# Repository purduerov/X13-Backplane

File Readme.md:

# Readme for X13-Backplane

Whenever you make a new part, download the datasheet and save it here _**and**_ with the part in the parts library

Always pull other people's changes before beginning to work
`git pull`

Be sure to push your changes after  working on them. Run:
1. `git add .` to add any files in this directory or a subdirectory
or `git add -u` to add any modified files
2. (Optional) `git clean -nX` to see what ignored files can be removed
	`git clean -fX` removes ignored files (Eagle backups)
3. `git commit -m "helpful commit message"` with a description of the work that you did
4. `git push` to push your work to github

Other helpful commands
* `git status` says information about modified and staged files
* `git log` shows the recent commits of the repository
* `git log filename.extension` show the recent commits for just that file
* `git checkout first-couple-letter-of-commit-id` lets you go back to a previous version
* `git checkout master` brings you back to the latest commit
* `git tag` lists the tags
* `git tag -a orderX -m "the version of the board placed for the X'th order"` tag a specific commit
* `git push --tags` needed to push tags to remote
* `git show orderX` show the commit log for the given tag
* `git checkout orderX` go back and interact with the files at the tagged commit

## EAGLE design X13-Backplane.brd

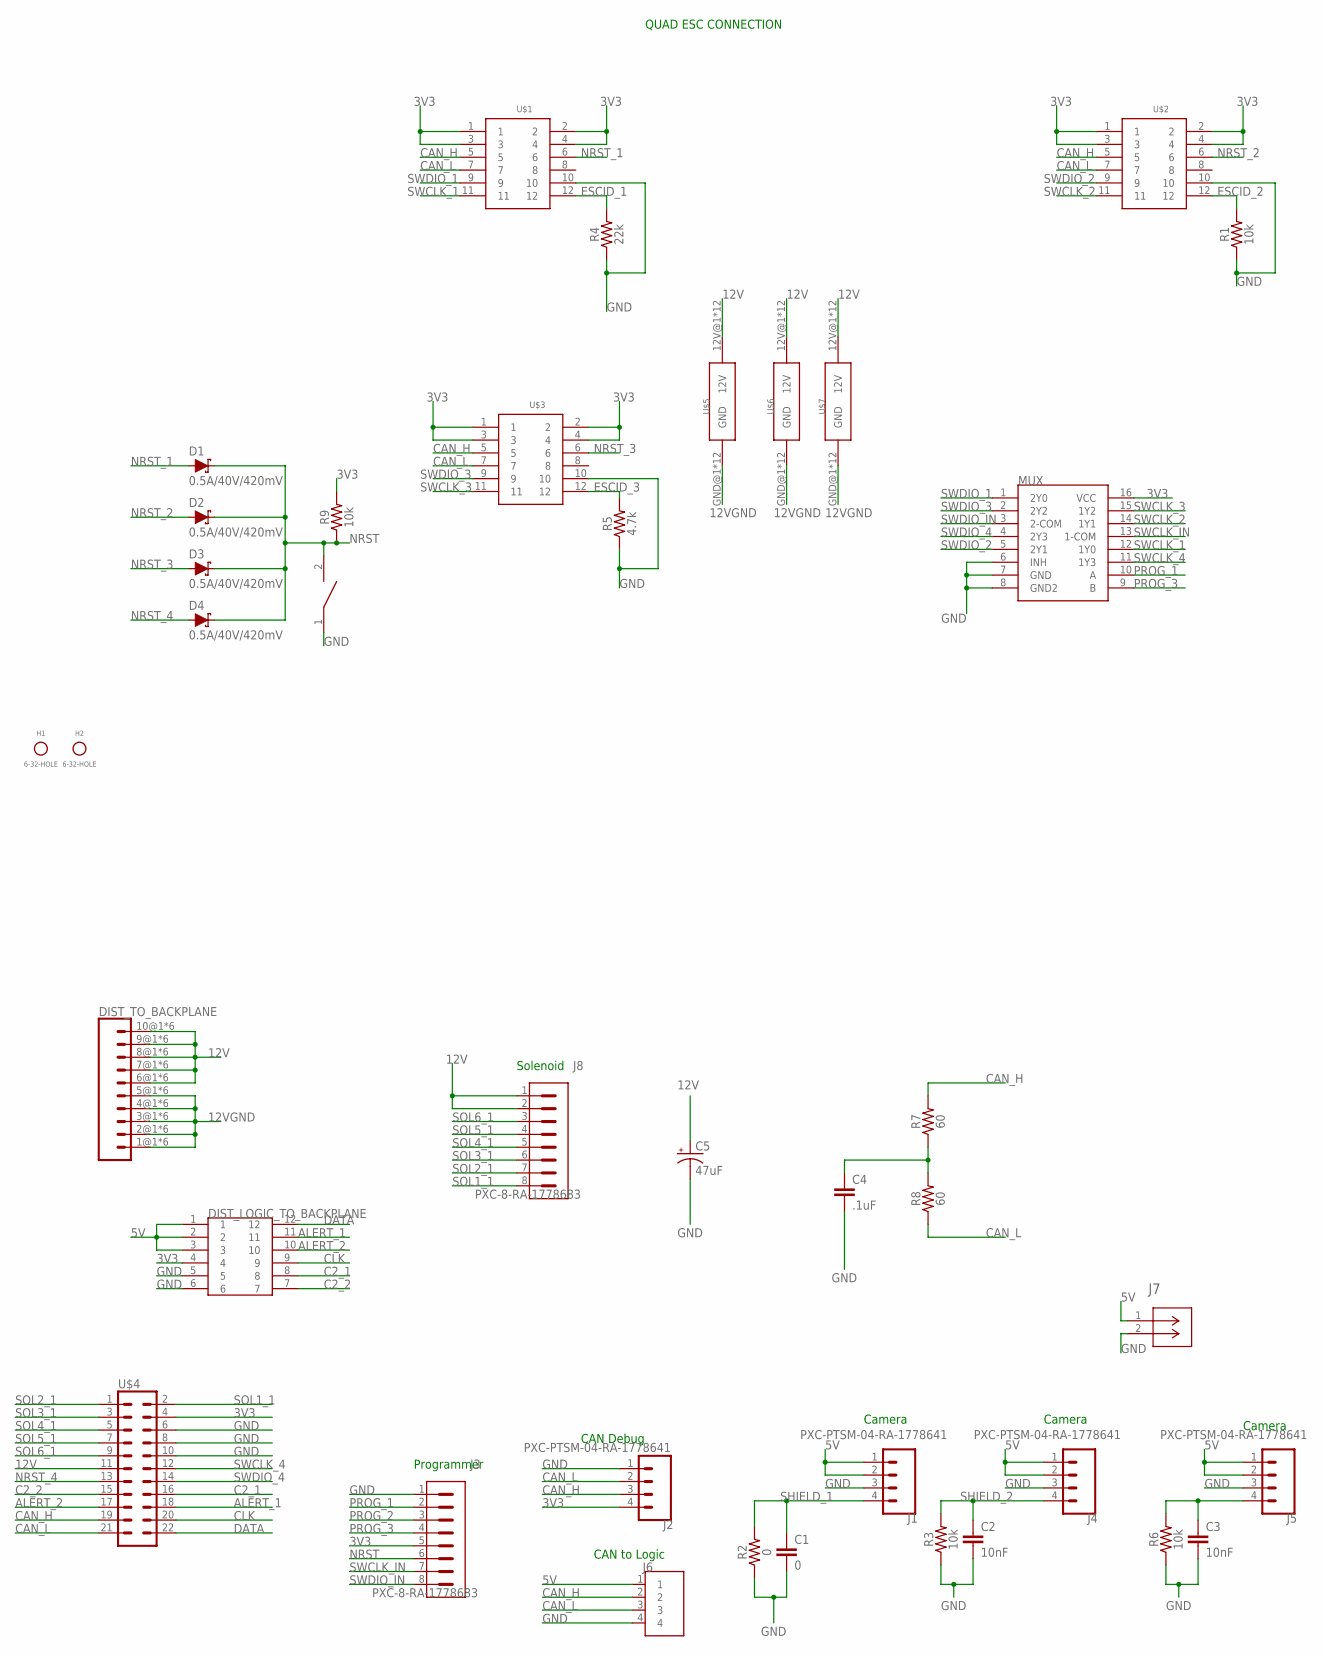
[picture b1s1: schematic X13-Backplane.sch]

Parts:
C1: 0; 0603
C2, C3: 10nF; 0603
C4: .1uF; 0603
C5: 47uF; PANASONIC_D
D1, D2, D3, D4: 0.5A/40V/420mV; SOD-323
DIST_LOGIC_TO_BACKPLANE: IPL1-106-01-L-D-K
DIST_TO_BACKPLANE: MPPT-10-01-01-L-RA-SD
H1, H2: 6-32-HOLE
J1, J2, J4, J5: PXC-PTSM-04-RA-1778641
J3, J8: PXC-8-RA-1778683
J6: 284512-4; TE_284512-4
J7: POE_TERMINAL; CONN2_282834-2_TEC
MUX: TI-SN74LV4052A; SOIC-16
R1, R3, R6, R9: 10k; 0603
R2: 0; 0603
R4: 22k; 0603
R5: 4.7k; 0603
R7, R8: 60; 0603
U$1, U$2, U$3: BACKPLANE_CONNECTORSBKP; BACKPLANE_CONNECTORS_BKP
U$4: BKP-TO-SOL; BKP-TO-SOL_TMM-111-01-T-D
U$5, U$6, U$7: BACKPLANE_ESC_ADAPTER_PWRBKP; BACKPLANE_ESC_ADAPTER_BKP_PWR
U$8: DISCRETECOMPONENTS_SWITCH; DISCRETECOMPONENTS_SW_2512

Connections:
3V3: DIST_LOGIC_TO_BACKPLANE.4, J2.4, J3.5, MUX.16 (VCC), R9.2, U$1.1, U$1.2, U$1.3, U$1.4, U$2.1, U$2.2, U$2.3, U$2.4, U$3.1, U$3.2, U$3.3, U$3.4, U$4.4
5V: DIST_LOGIC_TO_BACKPLANE.1, DIST_LOGIC_TO_BACKPLANE.2, DIST_LOGIC_TO_BACKPLANE.3, J1.1, J1.2, J4.1, J4.2, J5.1, J5.2, J6.1, J7.1
12V: C5.+, DIST_TO_BACKPLANE.6@1 (6), DIST_TO_BACKPLANE.6@2 (6), DIST_TO_BACKPLANE.6@3 (6), DIST_TO_BACKPLANE.6@4 (6), DIST_TO_BACKPLANE.6@5 (6), DIST_TO_BACKPLANE.6@6 (6), DIST_TO_BACKPLANE.7@1 (7), DIST_TO_BACKPLANE.7@2 (7), DIST_TO_BACKPLANE.7@3 (7), DIST_TO_BACKPLANE.7@4 (7), DIST_TO_BACKPLANE.7@5 (7), DIST_TO_BACKPLANE.7@6 (7), DIST_TO_BACKPLANE.8@1 (8), DIST_TO_BACKPLANE.8@2 (8), DIST_TO_BACKPLANE.8@3 (8), DIST_TO_BACKPLANE.8@4 (8), DIST_TO_BACKPLANE.8@5 (8), DIST_TO_BACKPLANE.8@6 (8), DIST_TO_BACKPLANE.9@1 (9), DIST_TO_BACKPLANE.9@2 (9), DIST_TO_BACKPLANE.9@3 (9), DIST_TO_BACKPLANE.9@4 (9), DIST_TO_BACKPLANE.9@5 (9), DIST_TO_BACKPLANE.9@6 (9), DIST_TO_BACKPLANE.10@1 (10), DIST_TO_BACKPLANE.10@2 (10), DIST_TO_BACKPLANE.10@3 (10), DIST_TO_BACKPLANE.10@4 (10), DIST_TO_BACKPLANE.10@5 (10), DIST_TO_BACKPLANE.10@6 (10), J8.1, J8.2, U$4.11, U$5.12V@1 (12V), U$5.12V@2 (12V), U$5.12V@3 (12V), U$5.12V@4 (12V), U$5.12V@5 (12V), U$5.12V@6 (12V), U$5.12V@7 (12V), U$5.12V@8 (12V), U$5.12V@9 (12V), U$5.12V@10 (12V), U$5.12V@11 (12V), U$5.12V@12 (12V), U$6.12V@1 (12V), U$6.12V@2 (12V), U$6.12V@3 (12V), U$6.12V@4 (12V), U$6.12V@5 (12V), U$6.12V@6 (12V), U$6.12V@7 (12V), U$6.12V@8 (12V), U$6.12V@9 (12V), U$6.12V@10 (12V), U$6.12V@11 (12V), U$6.12V@12 (12V), U$7.12V@1 (12V), U$7.12V@2 (12V), U$7.12V@3 (12V), U$7.12V@4 (12V), U$7.12V@5 (12V), U$7.12V@6 (12V), U$7.12V@7 (12V), U$7.12V@8 (12V), U$7.12V@9 (12V), U$7.12V@10 (12V), U$7.12V@11 (12V), U$7.12V@12 (12V)
12VGND: DIST_TO_BACKPLANE.1@1 (1), DIST_TO_BACKPLANE.1@2 (1), DIST_TO_BACKPLANE.1@3 (1), DIST_TO_BACKPLANE.1@4 (1), DIST_TO_BACKPLANE.1@5 (1), DIST_TO_BACKPLANE.1@6 (1), DIST_TO_BACKPLANE.2@1 (2), DIST_TO_BACKPLANE.2@2 (2), DIST_TO_BACKPLANE.2@3 (2), DIST_TO_BACKPLANE.2@4 (2), DIST_TO_BACKPLANE.2@5 (2), DIST_TO_BACKPLANE.2@6 (2), DIST_TO_BACKPLANE.3@1 (3), DIST_TO_BACKPLANE.3@2 (3), DIST_TO_BACKPLANE.3@3 (3), DIST_TO_BACKPLANE.3@4 (3), DIST_TO_BACKPLANE.3@5 (3), DIST_TO_BACKPLANE.3@6 (3), DIST_TO_BACKPLANE.4@1 (4), DIST_TO_BACKPLANE.4@2 (4), DIST_TO_BACKPLANE.4@3 (4), DIST_TO_BACKPLANE.4@4 (4), DIST_TO_BACKPLANE.4@5 (4), DIST_TO_BACKPLANE.4@6 (4), DIST_TO_BACKPLANE.5@1 (5), DIST_TO_BACKPLANE.5@2 (5), DIST_TO_BACKPLANE.5@3 (5), DIST_TO_BACKPLANE.5@4 (5), DIST_TO_BACKPLANE.5@5 (5), DIST_TO_BACKPLANE.5@6 (5), U$5.GND@1 (GND), U$5.GND@2 (GND), U$5.GND@3 (GND), U$5.GND@4 (GND), U$5.GND@5 (GND), U$5.GND@6 (GND), U$5.GND@7 (GND), U$5.GND@8 (GND), U$5.GND@9 (GND), U$5.GND@10 (GND), U$5.GND@11 (GND), U$5.GND@12 (GND), U$6.GND@1 (GND), U$6.GND@2 (GND), U$6.GND@3 (GND), U$6.GND@4 (GND), U$6.GND@5 (GND), U$6.GND@6 (GND), U$6.GND@7 (GND), U$6.GND@8 (GND), U$6.GND@9 (GND), U$6.GND@10 (GND), U$6.GND@11 (GND), U$6.GND@12 (GND), U$7.GND@1 (GND), U$7.GND@2 (GND), U$7.GND@3 (GND), U$7.GND@4 (GND), U$7.GND@5 (GND), U$7.GND@6 (GND), U$7.GND@7 (GND), U$7.GND@8 (GND), U$7.GND@9 (GND), U$7.GND@10 (GND), U$7.GND@11 (GND), U$7.GND@12 (GND)
ALERT_1: DIST_LOGIC_TO_BACKPLANE.11, U$4.18
ALERT_2: DIST_LOGIC_TO_BACKPLANE.10, U$4.17
C2_1: DIST_LOGIC_TO_BACKPLANE.8, U$4.16
C2_2: DIST_LOGIC_TO_BACKPLANE.7, U$4.15
CAN_H: J2.3, J6.2, R7.2, U$1.5, U$2.5, U$3.5, U$4.19
CAN_L: J2.2, J6.3, R8.1, U$1.7, U$2.7, U$3.7, U$4.21
CLK: DIST_LOGIC_TO_BACKPLANE.9, U$4.20
DATA: DIST_LOGIC_TO_BACKPLANE.12, U$4.22
ESCID_1: R4.2, U$1.12
ESCID_2: R1.2, U$2.12
ESCID_3: R5.2, U$3.12
GND: C1.2, C2.2, C3.2, C4.2, C5.-, DIST_LOGIC_TO_BACKPLANE.5, DIST_LOGIC_TO_BACKPLANE.6, J1.3, J2.1, J3.1, J4.3, J5.3, J6.4, J7.2, MUX.6 (INH), MUX.7 (GND), MUX.8 (GND2), R1.1, R2.1, R3.1, R4.1, R5.1, R6.1, U$1.10, U$2.10, U$3.10, U$4.6, U$4.8, U$4.10, U$8.1
unnamed: C4.1, R7.1, R8.2
NRST: D1.C, D2.C, D3.C, D4.C, J3.6, R9.1, U$8.2
NRST_1: D1.A, U$1.6
NRST_2: D2.A, U$2.6
NRST_3: D3.A, U$3.6
NRST_4: D4.A, U$4.13
PROG_1: J3.2, MUX.10 (A)
PROG_2: J3.3
PROG_3: J3.4, MUX.9 (B)
SHIELD_1: C1.1, J1.4, R2.2
SHIELD_2: C2.1, J4.4, R3.2
SHIELD_3: C3.1, J5.4, R6.2
SOL1_1: J8.8, U$4.2
SOL2_1: J8.7, U$4.1
SOL3_1: J8.6, U$4.3
SOL4_1: J8.5, U$4.5
SOL5_1: J8.4, U$4.7
SOL6_1: J8.3, U$4.9
SWCLK_1: MUX.12 (1Y0), U$1.11
SWCLK_2: MUX.14 (1Y1), U$2.11
SWCLK_3: MUX.15 (1Y2), U$3.11
SWCLK_4: MUX.11 (1Y3), U$4.12
SWCLK_IN: J3.7, MUX.13 (1-COM)
SWDIO_1: MUX.1 (2Y0), U$1.9
SWDIO_2: MUX.5 (2Y1), U$2.9
SWDIO_3: MUX.2 (2Y2), U$3.9
SWDIO_4: MUX.4 (2Y3), U$4.14
SWDIO_IN: J3.8, MUX.3 (2-COM)

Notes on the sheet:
CAN to Logic
CAN Debug
Programmer
QUAD ESC CONNECTION
Camera
Solenoid

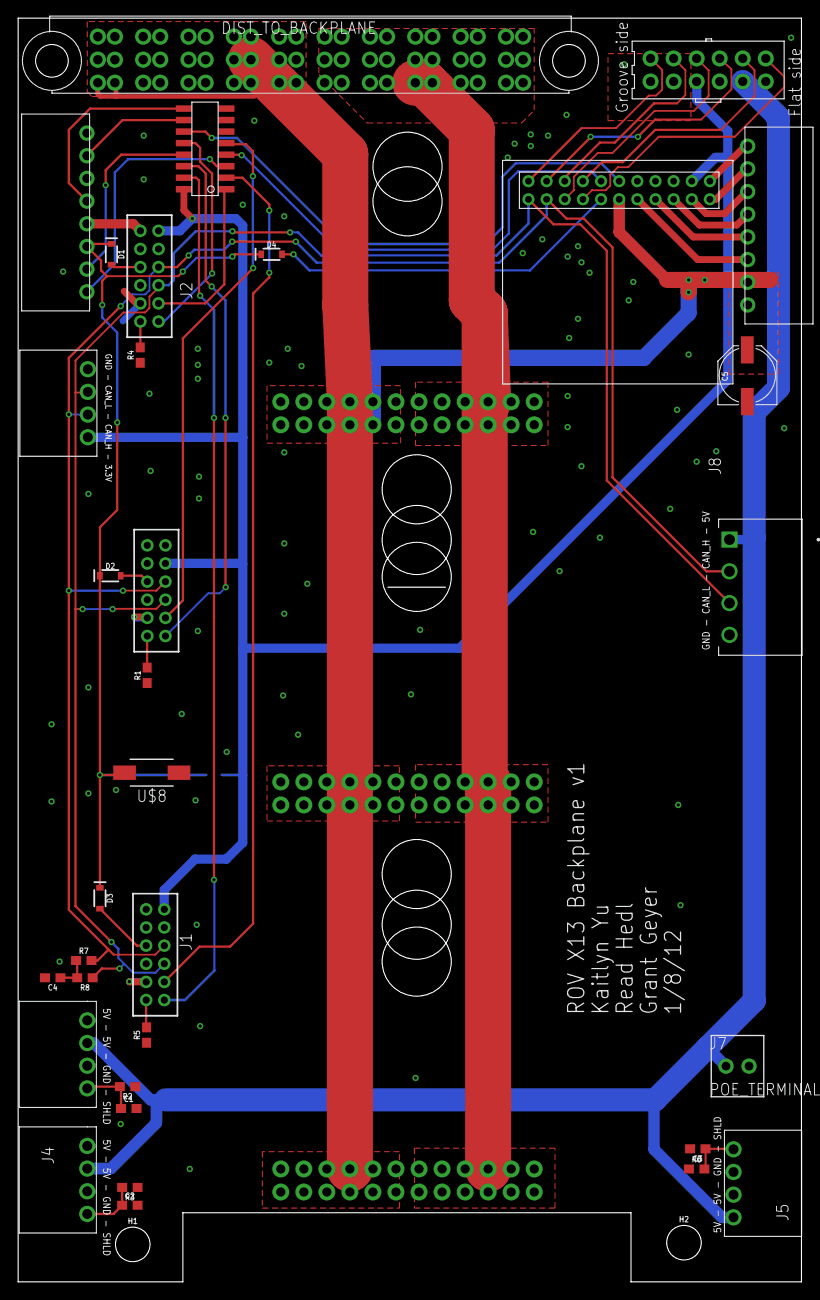
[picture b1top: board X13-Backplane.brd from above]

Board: 2 copper layers, 86.4 x 139.3 mm, 39 parts (1 on the bottom side), 43 nets.

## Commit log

2020-09-18 setup of repo
2020-10-21 first push
2020-10-21 Updated Solenoid Board
2020-10-24 added Thrusters/motor connectors + QuadESC Connectors
2020-10-25 remove DS Store file and ignore it
2020-10-31 Design review changes-2
2020-10-31 added LED resistor values
2020-11-01 board dimension
2020-11-14 draft board layout- missing power connector
2020-11-14 added back solenoid board
2020-11-14 removed solenoid board
2020-12-05 updated schematic
2020-12-05 wired board
2020-12-06 updated solenoid connector
2020-12-06 updated polygonsr
2020-12-06 updated via's
2020-12-06 updated mux
2020-12-06 updated 5v trace
2021-01-03 updated spacing on parts
2021-01-05 Placed Solenoid Connector and schematic pinout
2021-01-08 updated board layout and connections
2021-01-08 updated board
2021-01-08 added swclk/swdio signals to solenoid board
2021-01-08 added cutouts, adjusted gnd
2021-01-09 Added third cutout and models for te 4 pin conn
2021-01-09 add tStop polygon
2021-01-09 OPE. GND connections were missing on esc controller connector
2021-01-09 cleaned up traces
2021-01-09 integration
2021-01-10 Schematic PDF and step
2021-01-11 moved 2x6 logic dist block in and add conn for switch as backup
2021-01-12 re-add soldermask around connectors to adapter board
2021-01-20 Fixed misprinting of schematic
2021-05-03 Add reset switch for all micros, move connectors in
2021-05-04 Place resistor. Move solenoid connector in
2021-05-15 Change dimension to holes for ESC wires

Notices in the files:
parts and their libraries:
SparkFun-Resistors: Licensing: Creative Commons ShareAlike 4.0 International - https://creativecommons.org/licenses/by-sa/4.0
COPYRIGHT: Copyright (C) 2016 Accelerated Designs. All rights reserved
